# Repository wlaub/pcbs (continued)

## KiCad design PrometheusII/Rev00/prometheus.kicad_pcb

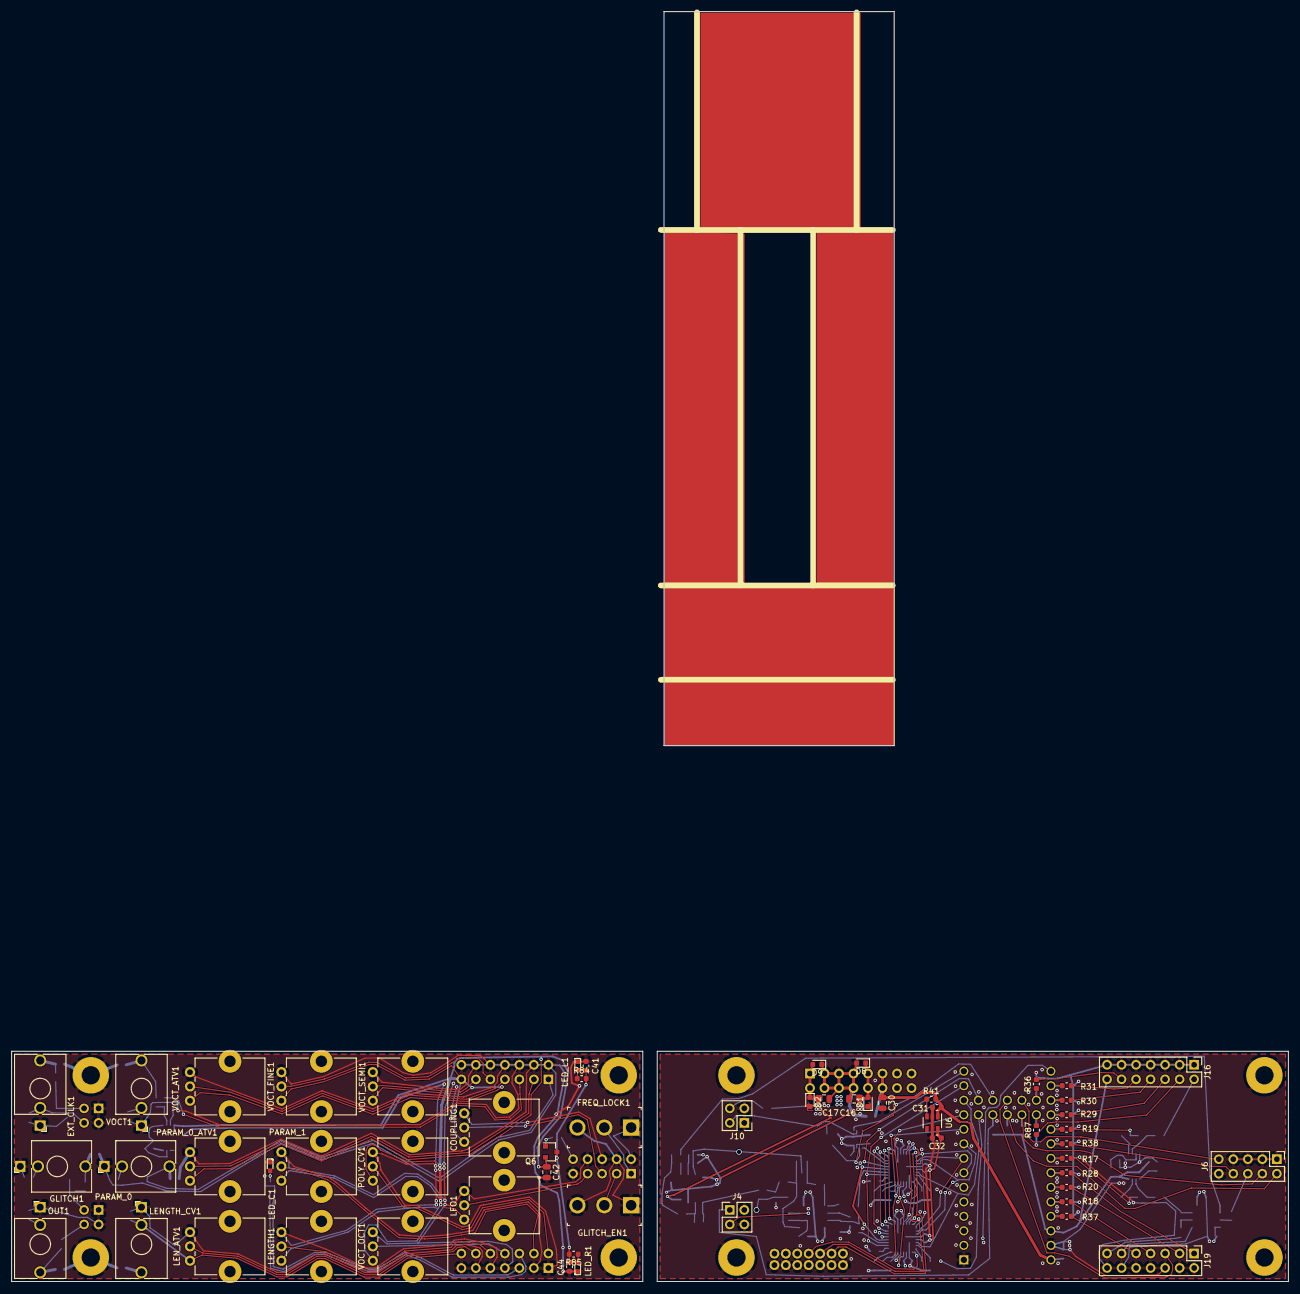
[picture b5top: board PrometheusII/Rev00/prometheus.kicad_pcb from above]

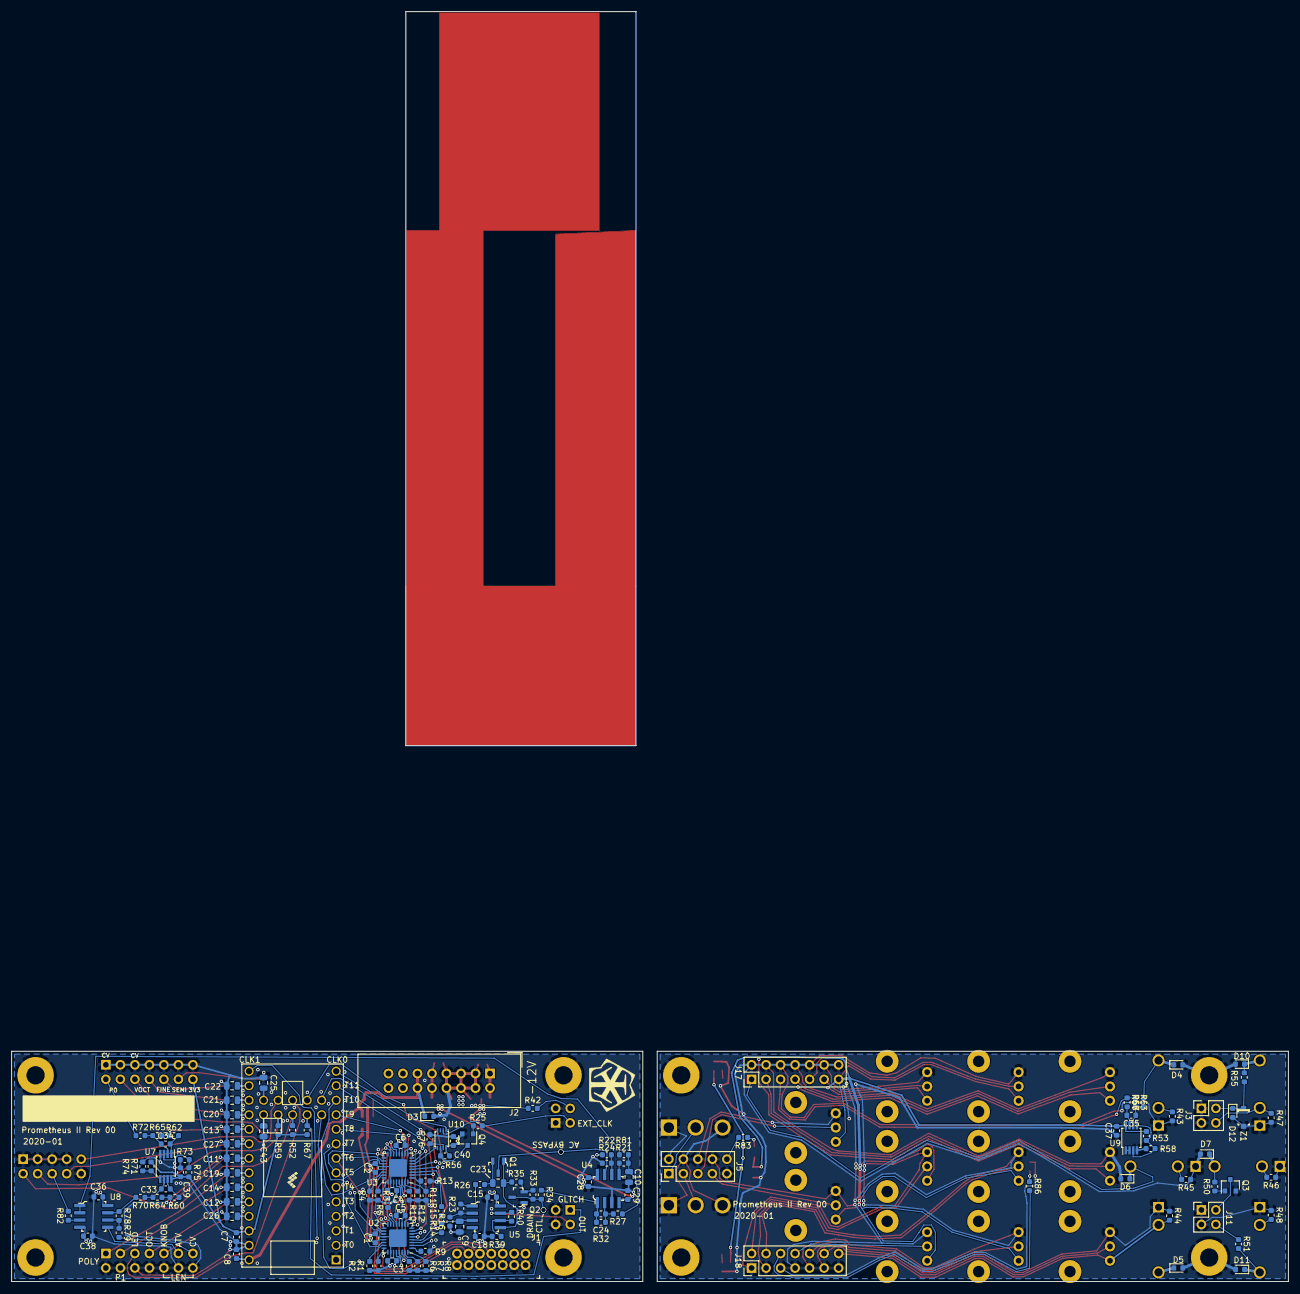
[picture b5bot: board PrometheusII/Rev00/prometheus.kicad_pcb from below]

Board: 4 copper layers, 194 parts (130 on the bottom side), 151 nets.

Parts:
C1, C2, C3, C4, C5, C6, C7, C8, C15, C18, C28, C29, C31, C32, C36, C37, C38, C39, C40, C41, C44: 1u; C_0603_1608Metric
C9, C10: 1n; C_0805_2012Metric
C11, C12, C13, C14, C19, C20, C21, C22, C25, C26, C27, C43: 100n; C_0805_2012Metric
C16, C17, C23, C30, C42: 10u; C_0805_2012Metric
C24, C33, C34, C35: 1n; C_0603_1608Metric
COUPLING1: 100k; Fixed_Potentiometer_Bourns_PTV09A-1_Single_Vertical
D1, D2, D12: SD0603S040S0R2; D_0603_1608Metric
D3, D4, D5, D6, D7, D8, D9, D10, D11: D_TVS; D_0603_1608Metric
EXT_CLK1: PJ398SM; Jack_3.5mm_QingPu_WQP-PJ398SM_Vertical_CircularHoles
FREQ_LOCK1: 100SP5T1B1M2QEH; Toggle_Switch_100SP1T1B4M2QE
GLITCH1: PJ398SM; Jack_3.5mm_QingPu_WQP-PJ398SM_Vertical_CircularHoles
GLITCH_EN1: 100SP5T1B1M2QEH; Toggle_Switch_100SP1T1B4M2QE
H1, H2, H3, H4, H5, H6, H7, H8: R30-1001102; MountingHole_3.2mm_M3_Pad
J1: 0878311420; PinHeader_2x7_P2mm_Drill1mm
J2: Conn_02x08_Odd_Even; IDC-Header_2x08_P2.54mm_Vertical
J3, J4, J10, J11: Conn_02x02_Odd_Even; PinHeader_2x02_P2.54mm_Vertical
J5, J6: Conn_02x05_Odd_Even; PinHeader_2x05_P2.54mm_Vertical
J16, J17, J18, J19: Conn_02x07_Odd_Even; PinHeader_2x07_P2.54mm_Vertical
LED_C1: LTST-C190KGKT; LED_0603
LED_L1: LTST-C190KGKT; LED_0603
LED_R1: LTST-C190KGKT; LED_0603
LENGTH1: 100k; Fixed_Potentiometer_Bourns_PTV09A-1_Single_Vertical
LENGTH_CV1: PJ398SM; Jack_3.5mm_QingPu_WQP-PJ398SM_Vertical_CircularHoles
LEN_ATV1: 100k; Fixed_Potentiometer_Bourns_PTV09A-1_Single_Vertical
LFO1: 100k; Fixed_Potentiometer_Bourns_PTV09A-1_Single_Vertical
OUT1: PJ398SM; Jack_3.5mm_QingPu_WQP-PJ398SM_Vertical_CircularHoles
PARAM_0: PJ398SM; Jack_3.5mm_QingPu_WQP-PJ398SM_Vertical_CircularHoles
PARAM_0_ATV1, PARAM_1: 100k; Fixed_Potentiometer_Bourns_PTV09A-1_Single_Vertical
POLY_CV1: 100k; Fixed_Potentiometer_Bourns_PTV09A-1_Single_Vertical
Q1, Q2: MMBF4391; SOT-23-3
Q3: BSS138; SOT-23
Q4, Q6: BSS84; SOT-23
R1, R2, R3, R4, R6, R7, R8, R9, R10, R11, R12, R13, R24, R32, R33, R34, R40, R42, R43, R44, R45, R46, R48, R52, R56, R59, R67, R70, R72, R78, R79: 100k; R_0603_1608Metric
R5, R16, R21, R23, R26, R35, R41, R76, R82: 0; R_0603_1608Metric
R14, R15, R22: 10k; R_0603_1608Metric
R17, R18, R19, R20, R28, R29, R30, R31, R36, R37, R38, R60, R62, R66, R84, R85, R87: 100; R_0603_1608Metric
R25, R50, R51, R55, R81, R83: 499; R_0603_1608Metric
R27, R47: 22k; R_0603_1608Metric
R39, R65: 33k; R_0603_1608Metric
R53: 31.6k .1%; R_0603_1608Metric
R57: 100k .1%; R_0603_1608Metric
R58: 14.9k .1%; R_0603_1608Metric
R63: 56k .1%; R_0603_1608Metric
R64: 18k; R_0603_1608Metric
R71: 75k; R_0603_1608Metric
R73: 15k; R_0603_1608Metric
R74: 102k; R_0603_1608Metric
R75: 24.9k; R_0603_1608Metric
R86: 330; R_0603_1608Metric
U1: Teensy4.0_NoSD; Teensy40_underpins
U2, U3: XC2C32A_LFSR; QFN-32-1EP_5x5mm_P0.5mm_EP3.1x3.1mm
U4, U5, U8: TL072CDR; SOIC-8_W3.9mm
U6: MIC5504-1.8YM5; SOT-23-5
U7, U9: MCP6002-xMS; MSOP-8_3x3mm_P0.65mm
U10: 74LVC2G157; VSSOP-8_2.4x2.1mm_P0.5mm
VOCT1: PJ398SM; Jack_3.5mm_QingPu_WQP-PJ398SM_Vertical_CircularHoles
VOCT_ATV1: 100k; Fixed_Potentiometer_Bourns_PTV09A-1_Single_Vertical
VOCT_FINE1: 100k; Fixed_Potentiometer_Bourns_PTV09A-1_Single_Vertical
VOCT_OCT1: 100k; Fixed_Potentiometer_Bourns_PTV09A-1_Single_Vertical
VOCT_SEMI1: 100k; Fixed_Potentiometer_Bourns_PTV09A-1_Single_Vertical
Z1: MMSZ5231B-7-F; SOD-123

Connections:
+1V8: C1.1, C2.1, C32.1, U2.21, U3.21, U6.5
+3V3: C3.1, C4.1, C5.1, C6.1, C7.1, C37.2, C39.2, C40.1, C42.1, COUPLING1.1, J16.14, J17.13, LENGTH1.1, LFO1.1, PARAM_0_ATV1.1, PARAM_1.1, POLY_CV1.1, Q6.2, R22.2, R52.2, R53.2, R56.2, R59.2, R67.2, R74.2, R75.2, U1.31, U2.12, U2.27, U3.12, U3.27, U7.8, U9.8, U10.8, VOCT_ATV1.1, VOCT_FINE1.1, VOCT_OCT1.1, VOCT_SEMI1.1
+5V: C8.1, C30.1, C31.1, D3.1, J2.11, J2.12, R41.1, U1.33, U6.1
+12V: C15.2, C16.1, C28.2, C36.1, D1.1, U4.8, U5.8, U8.8
-12V: C17.2, C18.1, C29.1, C38.2, D2.2, R42.1, U4.4, U5.4, U8.4
/CLK0: U3.6, U10.5
/CLK0_T: U1.14, U10.1
/CLK1_T: U1.20, U2.6
/CV_FILT: R81.2, U8.1, U8.2
/CV_FILT_P: COUPLING1.2, J5.5
/EXT_CLK: J10.2, R25.2, U10.2
/EXT_CLK_EN_T: Q4.3, R56.1, U1.38, U10.6
/EXT_CLK_P: D12.1, J3.2, R55.1, Z1.K
/EXT_CLK_SW: J10.4, R42.2
/EXT_CLK_SW_P: EXT_CLK1.TN, J3.4, R47.2
/FREQ_LOCK_P: FREQ_LOCK1.2, J5.1
/FREQ_LOCK_T: J6.2, R52.1, U1.42
/GLITCH_EN_P: GLITCH_EN1.2, J5.3
/GLITCH_EN_T: J6.4, R59.1, U1.41
/GLITCH_IN_P: J11.2, Q3.3
/GLITCH_IN_T: J4.1, R67.1, U1.43
/JTAG_TCK: J1.6, U2.16, U3.16
/JTAG_TDI: J1.10, U3.14
/JTAG_TDO: J1.8, U2.25
/JTAG_TDX0: R5.2, U3.25
/JTAG_TDX1: R5.1, U2.14
/JTAG_TMS: J1.4, U2.15, U3.15
/LEN_ATV: J19.11, U8.5
/LEN_ATV_P: J18.12, LEN_ATV1.2
/LEN_CV: R17.1, R60.1, R64.1
/LEN_CV_P: J18.14, LENGTH_CV1.TN, LEN_ATV1.1, R44.2
/LEN_CV_T: C11.1, R17.2, U1.26
/LEN_KNOB: J19.9, R37.1
/LEN_KNOB_P: J18.10, LENGTH1.2
/LEN_KNOB_T: C26.1, R37.2, U1.30
/LFO: J6.8, R38.1
/LFO_LED_P: J5.10, R83.2
/LFO_LED_T: J6.9, U1.36
/LFO_P: J5.7, LFO1.2
/LFO_T: C27.1, R38.2, U1.25
/LFSR0_IN: U1.39, U3.5
/LFSR1_IN: U1.44, U2.5
/OUT: J4.3, R40.1, U5.7
/OUT0: R15.2, U3.3
/OUT1: R14.1, U2.3
/OUTA: C9.1, R14.2, R15.1, U5.3
/OUTB: R23.2, R26.1, U5.1
/OUTC: C23.2, Q1.1, R35.2, U5.5
/OUT_P: J11.4, R51.1
/PARAM_0: J16.4, R87.1
/PARAM_0_CV: R19.1, R62.1, R65.1
/PARAM_0_CV_P: D6.1, J17.1, PARAM_0.T
/PARAM_0_CV_T: C13.1, R19.2, U1.24
/PARAM_0_P: J17.3, PARAM_0_ATV1.2
/PARAM_0_T: C43.1, R87.2, U1.40
/PARAM_1: J19.3, R20.1
/PARAM_1_P: J18.4, PARAM_1.2
/PARAM_1_T: C14.1, R20.2, U1.28
/POLY: J19.1, R28.1
/POLY_P: J18.2, POLY_CV1.2
/POLY_T: C19.1, R28.2, U1.27
/TAP0: U1.2, U2.7, U3.7
/TAP1: U1.3, U2.8, U3.8
/TAP2: U1.4, U2.9, U3.9
/TAP3: U1.5, U2.10, U3.10
/TAP4: U1.6, U2.13, U3.13
/TAP5: U1.7, U2.17, U3.17
/TAP6: U1.8, U2.18, U3.18
/TAP7: U1.9, U2.19, U3.19
/TAP8: U1.10, U2.29, U3.29
/TAP9: U1.11, U2.28, U3.28
/TAP10: U1.12, U2.22, U3.22
/TAP11: U1.13, U2.2, U3.2
/TAPS_LED_P: J18.6, R86.2
/TAPS_LED_T: J19.5, U1.37
/VJTAG: J1.2, U2.4, U3.4
/VOCT_ATV: J16.8, R30.1
/VOCT_ATV_P: J17.7, VOCT_ATV1.2
/VOCT_ATV_T: C21.1, R30.2, U1.22
/VOCT_CV: J16.6, R29.1
/VOCT_CV_P: J17.5, R63.1, R66.1
/VOCT_FINE: J16.10, R31.1
/VOCT_FINE_P: J17.9, VOCT_FINE1.2
/VOCT_FINE_T: C22.1, R31.2, U1.21
/VOCT_OCT: J19.7, R18.1
/VOCT_OCT_P: J18.8, VOCT_OCT1.2
/VOCT_OCT_T: C12.1, R18.2, U1.29
/VOCT_SEMI: J16.12, R36.1
/VOCT_SEMI_P: J17.11, VOCT_SEMI1.2
/VOCT_SEMI_T: C25.1, R36.2, U1.35
/VOCT_T: C20.1, R29.2, U1.23
/_CV_FILT: J6.6, R82.2
/_LEN_CV: J19.13, R79.2
/_PARAM_0_CV: J16.2, R72.2
GND: C1.2, C2.2, C3.2, C4.2, C5.2, C6.2, C7.2, C8.2, C9.2, C10.2, C11.2, C12.2, C13.2, C14.2, C15.1, C16.2, C17.1, C18.2, C19.2, C20.2, C21.2, C22.2, C25.2, C26.2, C27.2, C28.1, C29.2, C30.2, C31.2, C32.2, C36.2, C37.1, C38.1, C39.1, C40.2, C41.2, C42.2, C43.2, C44.2, COUPLING1.3, D3.2, D4.2, D5.2, D6.2, D7.2, D8.2, D9.1, D10.2, D11.2, D12.2, EXT_CLK1.S, FREQ_LOCK1.1, FREQ_LOCK1.3, GLITCH1.S, GLITCH_EN1.1, GLITCH_EN1.3, H1.1, H2.1, H3.1, H4.1, H5.1, H6.1, H7.1, H8.1, J1.1, J1.3, J1.5, J1.7, J1.9, J1.11, J1.13, J2.3, J2.4, J2.5, J2.6, J2.7, J2.8, J3.1, J3.3, J4.2, J4.4, J5.2, J5.4, J5.6, J5.8, J5.9, J6.1, J6.3, J6.5, J6.7, J6.10, J10.1, J10.3, J11.1, J11.3, J16.1, J16.3, J16.5, J16.7, J16.9, J16.11, J16.13, J17.2, J17.4, J17.6, J17.8, J17.10, J17.12, J17.14, J18.1, J18.3, J18.5, J18.7, J18.9, J18.11, J18.13, J19.2, J19.4, J19.6, J19.8, J19.10, J19.12, J19.14, LED_C1.1, LED_L1.1, LED_R1.1, LENGTH1.3, LENGTH_CV1.S, LEN_ATV1.3, LFO1.3, OUT1.S, PARAM_0.S, PARAM_0_ATV1.3, PARAM_1.3, POLY_CV1.3, Q2.1, Q3.2, Q4.2, R1.2, R2.2, R3.2, R4.2, R6.1, R7.1, R8.1, R9.1, R10.1, R11.1, R12.1, R13.1, R16.1, R24.2, R39.1, R43.1, R44.1, R45.1, R46.1, R47.1, R48.1, R58.1, R71.1, R73.1, R76.1, U1.1, U1.32, U2.11, U2.20, U2.26, U2.33, U3.11, U3.20, U3.26, U3.33, U4.3, U6.2, U7.4, U9.4, U10.4, VOCT1.S, VOCT_ATV1.3, VOCT_FINE1.3, VOCT_OCT1.3, VOCT_SEMI1.3, Z1.A
unnamed: C10.1, R21.2, R27.2, R81.1
unnamed: C23.1, Q1.2, R26.2
unnamed: C24.1, R32.1, R34.1, U4.1
unnamed: C24.2, R27.1, R32.2, U4.2
unnamed: C33.1, R64.2, R70.1, U7.6
unnamed: C33.2, R60.2, U7.7
unnamed: C34.1, R65.2, R72.1, U7.2
unnamed: C34.2, R62.2, U7.1
unnamed: C35.1, R57.1, R63.2, U9.6
unnamed: C35.2, R66.2, U9.7
unnamed: C41.1, C44.1, Q6.3, R84.2, R85.2
unnamed: D1.2, D8.1, J2.9, J2.10
unnamed: D2.1, D9.2, J2.1, J2.2
unnamed: D4.1, R57.2, VOCT1.T
unnamed: D5.1, LENGTH_CV1.T
unnamed: D7.1, GLITCH1.T, R50.2
unnamed: D10.1, EXT_CLK1.T, R55.2
unnamed: D11.1, OUT1.T, R51.2
unnamed: GLITCH1.TN, R46.2
unnamed: LED_C1.2, R86.1
unnamed: LED_L1.2, R84.1
unnamed: LED_R1.2, R85.1
unnamed: OUT1.TN, R48.2
unnamed: PARAM_0.TN, R45.2
unnamed: Q1.3, U4.7
unnamed: Q2.2, R33.2, R35.1
unnamed: Q2.3, R33.1, R34.2
unnamed: Q3.1, R50.1
unnamed: Q4.1, R25.1
unnamed: Q6.1, R83.1
unnamed: R1.1, U2.24
unnamed: R2.1, U2.23
unnamed: R3.1, U3.24
unnamed: R4.1, U3.23
unnamed: R6.2, U2.30
unnamed: R7.2, U2.31
unnamed: R8.2, U2.32
unnamed: R9.2, U2.1
unnamed: R10.2, U3.30
unnamed: R11.2, U3.31
unnamed: R12.2, U3.32
unnamed: R13.2, U3.1
unnamed: R16.2, R23.1, U5.2
unnamed: R21.1, U4.5
unnamed: R22.1, R24.1, U4.6
unnamed: R39.2, R40.2, U5.6
unnamed: R41.2, U6.3
unnamed: R43.2, VOCT1.TN
unnamed: R53.1, R58.2, U9.3, U9.5
unnamed: R70.2, R78.1, U8.7
unnamed: R71.2, R74.1, U7.5
unnamed: R73.2, R75.1, U7.3
unnamed: R76.2, U10.7
unnamed: R78.2, R79.1, U8.6
unnamed: R82.1, U8.3
unnamed: U9.1, U9.2

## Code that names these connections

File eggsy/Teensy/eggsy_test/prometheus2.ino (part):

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int glitch_taps;

int sck_pin = 2;
int sdo_pin = 4;
int sdi_pin = 3;
int we_pin = 5;

void write_lfsr(unsigned short taps, unsigned char oe0, unsigned char oe1)
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  {
    
    digitalWrite(sck_pin, 0);
    digitalWrite(sdi_pin, data>>15);
    digitalWrite(sck_pin, 1);
    data <<= 1;
    
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  {
        
    result<<=1;
    result|=digitalRead(sdo_pin);
    digitalWrite(sck_pin, 1);
    digitalWrite(sck_pin, 0);
    
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  analogWriteFrequency(clk_pin_1, 100e3);
  analogWriteResolution(2);
  analogWrite(clk_pin_0, 2);
  pinMode(lfsr0_in_pin, OUTPUT);
  pinMode(lfsr1_in_pin, OUTPUT);
  digitalWrite(lfsr0_in_pin, 1);
  digitalWrite(lfsr1_in_pin, 1);

  INIT_OUTPUT(lfo_led_pin, 0)
  //INIT_OUTPUT(led0_pin, 0)
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  pinMode(freq_lock_pin, INPUT);
  //pinMode(ext_clk_en_pin, INPUT);

  pinMode(voct_atv_pin, INPUT);
  pinMode(voct_fine_pin, INPUT);
  pinMode(voct_cv_pin, INPUT);
  pinMode(param_0_pin, INPUT);
  pinMode(param_0_cv_pin, INPUT);
  pinMode(len_cv_pin, INPUT);
  pinMode(lfo_pin, INPUT);
  pinMode(param_1_pin, INPUT);
  pinMode(len_knob_pin, INPUT);
  pinMode(poly_sw_pin, INPUT);


  configure_adc();
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  //Setup serial interface pins
  pinMode(we_pin, OUTPUT); //Active high write enable
  pinMode(sck_pin, OUTPUT);
  pinMode(sdo_pin, INPUT); //LFSR serial data out to MCU
  pinMode(sdi_pin, OUTPUT); //LFSR serial data in from MCU
  //Initialize LFSR
  write_lfsr(0x1, lfsr_en0,lfsr_en1);
  
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    
  }

  poly = 0;
  if(poly_enc_counter > 0)
  {
    poly = (poly_enc_counter-1)%poly_count;
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  int voct_cv;
//  //int voct_oct; GLOBAL

  voct_fine = adc_memory[pin_to_channel[voct_fine_pin]];
  //voct_cv = adc_memory[pin_to_channel[voct_cv_pin]];
  //voct_atv = adc_memory[pin_to_channel[voct_atv_pin]];

  int param_0;
  int param_0_cv;
  int param_1;
  
  param_0 = adc_memory[pin_to_channel[param_0_pin]];
  param_0_cv = adc_memory[pin_to_channel[param_0_cv_pin]];
  param_1 = adc_memory[pin_to_channel[param_1_pin]];

  int len_knob;
  int len_cv;
  len_knob = adc_memory[pin_to_channel[len_knob_pin]];
  len_cv = adc_memory[pin_to_channel[len_cv_pin]];

  freq_lock = 1 - digitalRead(freq_lock_pin);
  
//  
//  /*  Serial.print(voct_cv);
//    Serial.print(",");
//    Serial.print(adc_memory[pin_to_channel[poly_pin]]);
//    Serial.print(",");
//*/
//    /*
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//    Serial.print(lfo);
//
//    Serial.print(",");
//    Serial.print(adc_memory[pin_to_channel[voct_oct_pin]]);
//
//
//    Serial.print(",");
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  int new_taps;

  int lfo;
  lfo = adc_memory[pin_to_channel[lfo_pin]];

  float lfo_result;
  lfo_result = pow(2,4.32*float(lfo)/(half)); //20 Hz to 1 Hz at center = 20 to 1/20Hz. log_2(400)= 8.64
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  }


  //digitalWrite(lfsr1_in_pin, 0); //Uninverts LFSR1 during glitch, kinda buggy?
  if (glitch_counter > 0)
  {
    //digitalWrite(lfsr1_in_pin, 1); //Uninverts LFSR1 during glitch, kinda buggy/ tends to stick?
    glitch_counter -= 1;
    actual_len=2048; //To freq lock during glitch
    new_taps = glitch_taps;
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  /*Deadzone at zero*/
  if (voct_fine > -zero and voct_fine < zero)
  {
    voct_fine = 0;
    //digitalWrite(XXX, 1); //This is where you would indicate deadzone if you had a light
  }
  else if (voct_fine <= -zero)
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
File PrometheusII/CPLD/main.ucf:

#PACE: Start of Constraints generated by PACE

#PACE: Start of PACE I/O Pin Assignments
NET "CLK0"  LOC = "P3"  ; 
NET "CLK1"  LOC = "P1"  ; 
NET "CLK_SEL"  LOC = "P23"  ;
NET "EXT_CLK"  LOC = "P27"  ; 
NET "INPUT0"  LOC = "P36"  ;
NET "INPUT1"  LOC = "P37"  ;
NET "IO<0>"  LOC = "P28"  ;
NET "IO<1>"  LOC = "P29"  ;
NET "IO<2>"  LOC = "P30"  ;
NET "IO<3>"  LOC = "P31"  ;
NET "IO<4>"  LOC = "P32"  ;
NET "IO<5>"  LOC = "P33"  ;
NET "IO<6>"  LOC = "P34"  ;
NET "OUTPUT0"  LOC = "P21"  ; 
NET "OUTPUT1"  LOC = "P19"  ; 
NET "SCK"  LOC = "P43"  ; 
NET "SDI"  LOC = "P42"  ; 
NET "SDO"  LOC = "P40"  ;
NET "WE"  LOC = "P39"  ;

#PACE: Start of PACE Area Constraints

#PACE: Start of PACE Prohibit Constraints

#PACE: End of Constraints generated by PACE

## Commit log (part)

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2019-12-24 Added prometheus ii files to repo
2019-12-24 Added library files to repo
2019-12-26 Added simulation models
2019-12-26 Added analog path simulation
2019-12-26 Added 1.8V supply, updated to use 16-pin connector for 5V
2019-12-26 Implemented analog output signal chain
2019-12-27 Started controls
2019-12-27 Finished CV inputs
2019-12-27 Fixed missing attenuverters
2019-12-27 Added anti-aliasing/sampling filters and some notes
2019-12-27 Finished control panel sheet
2019-12-27 Added optional ext clk buffer
2019-12-27 connect panel controls to main schematic
2019-12-27 Marked DNP Parts
2019-12-27 Exported schematic
2019-12-27 Annotated schematic
2019-12-28 Separated chance CV and Knob
2019-12-28 Started panel layout
2019-12-28 spread panel a little
2019-12-28 sorted components
2019-12-28 Updated panel layout
2019-12-28 rough board to board connector placement
2019-12-28 header unification
2019-12-28 header deunification
2019-12-28 jack circuitry placement
2019-12-29 Placed lfo indicator circuitry
2019-12-29 Split signal nets across boards
2019-12-29 SChematic update to move some buffers to other board
2019-12-29 setup second board outline
2019-12-29 rough placement of output stage, logic, connectors
2019-12-30 first pass rough placement
2019-12-30 shrank bottoms edge connectors to make room for standoffs
2019-12-30 Added standoff landings
2019-12-30 revised board connections
2019-12-31 recongfigured pinouts
2019-12-31 lfsr + clock placement work
2019-12-31 output buffer placement
2019-12-31 filter control placement
2019-12-31 clock sel and logic supply placement
2019-12-31 len/filt cv buffer placement
2020-01-01 placement tuning
2020-01-01 Fixed connector placement
2020-01-01 more pinout work
2020-01-01 controls board placement finished
2020-01-01 Fixed oversized footprint
2020-01-03 main board top section signal routing
2020-01-03 most power supply routing
2020-01-04 CIB signal routing finished
2020-01-04 CIB ground pours
2020-01-04 working ground planes on MB0
2020-01-04 DRC time
2020-01-04 resolved legitimate DRCs
2020-01-04 fixed unconnected net DRCs and tweaked panel placement
2020-01-04 silkscreen labelling
2020-01-04 Fixed too small of viases
2020-01-04 some more silkscreens
2020-01-04 couple more silk screens
2020-01-04 tuned power supply routing a bit
2020-01-04 fixed npth in pot footprint
2020-01-04 updated pot footprints in design
2020-01-04 Added panel holes
2020-01-04 Added mounting holes
2020-01-04 Initial panel design
2020-01-04 Updated schematic annotations
2020-01-04 added mounting hole ftpt
2020-01-04 gitignore updates
2020-01-06 headers
2020-01-06 everything except passives
2020-01-06 resistor part numbers
2020-01-06 capacitors - need to update footprints in layout at some point to be 0603 and not 0805 1n caps
2020-01-12 schematic pdf update
2020-01-13 cpld source files
2020-01-13 Added teensy code
2020-01-14 work on software
2020-01-14 most teensy codes
2020-01-20 Working on ADCs
2020-01-20 Fixed taps led issue
2020-01-21 ADC's working, implemented remaining CV's (len still needs hardware fix)
2020-01-21 Fixed poly pin not read
2020-01-26 Fixed phantom clock
2020-01-26 added deadzone at 0 on v/oct atten knob
2020-02-01 Locked Rev00
2020-02-01 Begin Rev01
2020-02-01 Remove discrete clk mux, Fix MB0 connector orientation, fix jack detect circuit
2020-02-01 Fix length cv input connectivity
2020-02-01 Stronger v/oct pulldown on switch
2020-02-01 Updated CPLD project files
2020-02-01 Updated naming to make better sense
2020-02-01 Fixed naming for real
2020-02-01 new CPLD symbol
2020-02-01 Serial LFSR CPLD symbol
2020-02-01 Implemented new CPLD
2020-02-01 Fixed some missing connections, added test points around CPLD
2020-02-01 A little more schematic cleanup, ready to start on hard choices
2020-02-04 Added IO expander
2020-02-08 Adding timing functions and serial test
2020-02-08 Fixed overflow issue in length selection
2020-02-08 Fixed LFO rate for new loop period units
2020-02-09 Started encoder implementation - the rest will have to wait for layout updates
2020-02-16 CPLD placement
2020-02-16 reworking output stage layout
2020-02-17 Revised gain portion of output filter to permit guard trace
2020-02-17 got all components back on board
2020-02-17 working on cpld routing
2020-02-17 CPLD signal routing
2020-02-17 CPLD power supply routing
2020-02-17 Changed switch PN, keeping footprint the same for now
2020-02-17 put fiducials in design
2020-02-17 Fixed analog signal assigned to non-analog pin
2020-02-17 Working on connector updates
2020-02-17 Updated connector placement and footprints
2020-02-17 Routed output filter, updated bottom side connector pinouts
2020-02-18 output stage power routing
2020-02-18 Starting on top half placement fixed
2020-02-18 assigned nets to new connectors
2020-02-18 Moved connectors back onto schematic
2020-02-18 some connection optimizations
2020-02-18 Added extra LEDs
2020-04-06 Updated to 6 LEDs + charlieplexing
2020-04-07 Some supply and signal routing
2020-04-07 Additional power supply routing
2020-04-07 Some minor routing
2020-04-07 Starting CIB routing
2020-04-07 python for computing tangents to circles
2020-04-08 Move tangents script
2020-04-08 Fixed another error
2020-04-08 Some routing
2020-04-08 Updated pot footprints to reduce AR on component side
2020-04-08 Made plugins/buttons for routing simple tangents
2020-04-08 icon for point tangents
2020-04-08 Added point to circle tangents button
2020-04-08 Updated inner/outer tangents to select the set with the endpoint nearest the grid origin
2020-04-09 Added bus node creation
2020-04-09 Fixed a couple things
2020-04-09 another fix
2020-04-09 End of day checkpoint
2020-04-09 Update to use user units
2020-04-09 Updated to allow non-pad node centers
2020-04-09 reorged CIB schematic for readability, added pot decoupling and filtering caps
2020-04-09 Move switch glitch capacitors to controls board, removed extra filter on ext clk
2020-04-09 Placed glitch caps on CIB
2020-04-09 Added net spreading button
2020-04-09 Some additional routing
2020-04-09 adding nodes won't overlap traces anymore
2020-04-10 Base logic for arc completion works?
2020-04-10 Refactor bus tangent finding to allow for including layers
2020-04-10 Implemented automatic side selection for circle to circle tangent routing based on bus layer
2020-04-10 Added side selection for point tangents
2020-04-10 Updated arc completion to merge nets
2020-04-10 Some routing with arc completion
2020-04-10 Fixed arc orientation issue
2020-04-10 Fixed not checking only selected tracks
2020-04-10 Top side analog bus routing complete
2020-04-10 Some more top side touchup
2020-04-10 minor tweak
2020-04-11 Fixed width default, and made clearance value persistent in node creation
2020-04-11 Routing rework around jacks
2020-04-11 Additional silkscreen and routing cleanup
2020-04-11 Updated LED placement
2020-04-11 Routed supplies
2020-04-11 refactored power supplies somewhat
2020-04-11 Initial layout of controls integration board finished?
2020-04-19 indicator LED layout finished, added extra orange LED to schematic + changed middle column LEDs to orange
2020-04-19 Placed new LED on board
2020-04-19 Some top-side ground plane cleanup
2020-04-19 Bottom side ground plane cleanup
2020-04-19 Added decoupling caps to power supplies on connectors
2020-04-20 switching to main board, some routing revisions using new functions
2020-04-20 minor silk
2020-04-20 Moved glitch_en on header to improve routing
2020-04-20 Routed CV filt across board
2020-07-11 Ripping up for new connector layout
2020-07-12 It's going to be a long night
2020-07-12 Additional tweaks
2020-07-12 Flipped teensy, moved jtag to pogo pin contacts, moved power connector to opposite edge
2020-07-12 Move bus nodes to ECO layers
2020-07-13 Some supply routing
2020-07-13 Additional routing
2020-07-13 Additional routes
2020-07-14 Additional routes, gonna try spreading out encoder pullups
2020-07-14 Encoder pullups placed and routed
2020-07-14 JTAG routing
2020-07-14 Power supply routing
2020-07-14 More layout reworks
2020-07-16 couple vias
2020-07-17 Fixed analog pins
2020-07-17 routing
2020-07-18 Pinout reshuffling
2020-07-18 Fixed additional header footprints
2020-07-18 Added button to flip ECO guides
2020-07-18 some refactoring
2020-07-19 Panel stuff
2020-07-19 Starting CIB cleanup
2020-07-19 models for panel components
2020-07-19 CIB supply routing rework
2020-07-20 routing, tweaking, fiddling
2020-07-20 Added LED model
2020-07-20 some silkscreen cleanup
2020-07-23 Started shiftclone button, still need to add direction control
2020-07-24 shift clone finished
2020-07-25 extend to circle
2020-07-26 LED routing
2020-07-26 some sketching
2020-07-27 CIB routing finished?
2020-07-27 LED routing tweak
2020-07-27 fixed interrupted ground pour
2020-07-28 everything is connected
2020-07-28 various minor fixes
2020-07-28 going to rotate everything to fix silkscreen orientation
2020-07-28 rotated everything to fix silkscreen orientation
2020-07-29 silkscreen first pass
2020-07-29 jlc location on main board
2020-07-29 Silkscreen done?
2020-07-29 Fixed there being some pad around upper row of jack holes
2020-07-31 Full archive of rev 0 exports, fab outputs
2020-08-01 Various DRC fixes
2020-08-01 Some schematic cleanup
2020-08-01 ADC matching amp simulation
2020-08-02 Part selection
2020-08-02 Some filtering annotations and changes
2020-10-02 woops
2020-12-01 JTAG to pogo pin adapter board
2020-12-01 gerbs for jtag adapter
2020-12-09 Look i just need there to be an up to date schematic in the repo okay jesus
2020-12-10 end of day 1
2020-12-25 read/write to LFSR
2020-12-25 latest cpld code
2020-12-26 Wired up fine tuning knob, implemented encoder tracking, wired up semi/oct encoders
2020-12-26 some cleanup
2021-01-08 poly knob work
2021-01-08 poly knob work more better
2021-02-02 splitting things up, working on adc interleaving, measuring sample rate, reducing teensy power consumption
2021-02-02 heavier filtering, nicer printing
2021-04-03 dumping some files that might have been missing
2021-04-03 starting on Eggsy I
2021-04-03 copying prom 2 code for starting place to prototype scope code
2021-04-03 names
2021-04-04 block diagram update
2021-04-04 Top level schematic
2021-04-04 schematic cleanup + 2 status leds
2021-04-04 typo fix
2021-04-04 little more cleanup
2021-04-10 manually adding ports to schematics, thx kicad
2021-04-10 power entry/exuent
2021-08-20 length lock mode allows scrolling through lengths with poly knob
2021-08-20 moving poly knob while pressed prevents tapping function
2021-08-20 please only cycle through length when length lock is selected, and the knob is not pressed
2021-08-25 length led blinks when knob equals locked length, and poly mode select led blinks after holding switch for 5 seconds
2021-08-25 long-press poly knob in polyphony mode to reset
2021-08-25 long-press in reset mode to reset all encoders
2021-08-30 Updated to use semi/oct knobs for configuring lfsr1 pitch, push mfe to toggle on and off
2021-08-31 lfsr1 pitch relative to lfsr0 pitch
2021-08-31 rearranged controls, replaced param_0 cv control with fm cv control
2021-08-31 blink pitch knobs to indicate polyphony mode
2021-09-01 simplified led configuration a bit
2021-09-01 optimized FM/adc interrupt handling
2021-09-01 Added missing config.h
2021-09-01 additional optimizations
2021-09-02 even more of adc isp performance improvements
2021-09-02 implemented global config flag controls + fast blinker
2021-09-02 implemented config option to select between param0 cv and fm cv
2021-09-02 Move detune setting to UC LED
2021-09-02 Changed adc interrupt to do computations on every run for more consistent sample rate, cut filtering in half to compensate
2021-09-09 updated plotting script, add baseline data
2021-09-09 script to plot decay time vs time of measurement
2021-09-09 errorbars
2021-09-10 0.47 uF data
2021-09-11 part variation data
2021-09-11 more comparison data
2021-09-14 more curving
2021-09-14 getting ready for per-curve parameters
2021-09-15 independent parameter adjustment per curve
2021-09-19 constant current mode filter stuff
2023-03-13 teensy to neopixel breakout board
2023-03-25 start on driver software
2023-03-25 update to support all led outputs
2023-03-26 add led-end breakout board
